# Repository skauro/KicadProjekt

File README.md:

# Raspberry Pi GPIO Hat – For raspberry pi 4B based prototype that measures video delay

This repository contains the complete KiCad project files, Gerber output, and a .rar archive package intended for PCB manufacturing and modification. The design is a custom Raspberry Pi HAT (Hardware Attached on Top) tailored for GPIO interfacing with USB and RJ45 port alignment for an enclosure.

## 📷 Overview
 It features:
 
- **Raspberry Pi 40-pin GPIO header** for direct stacking.
- **Two push-button switches**:
  - `SW1`: Momentary tactile push button
  - `SW2`: SPDT switch footprint
- **Supporting components**:
  - Capacitors (10µF, 100nF) for decoupling
  - Resistors (e.g., 10Ω) for current limiting or signal conditioning
  - LED (D2) indicator
- A mostly top-layer signal layout with a ground pour to ensure good electrical performance.

## 📁 Contents
├── gerber/ # Gerber files for manufacturing

├── *.kicad_sch # Schematic

├── *.kicad_pcb # PCB layout

├── Gerbers.rar # Pre-packaged archive to send to PCB manufacturer

└── README.md # This file

🛠️ How to Use
For Fabrication:
Send the contents of the Gerbers.rar or the /gerber/ folder to your preferred PCB manufacturer. Most PCB suppliers accept this standard format.

For Modification:
Clone or download this repository.

Open the .kicad_pro file using KiCad (version 7+ recommended).

Modify the schematic or PCB layout as needed.

Re-export the Gerber files from KiCad.

📦 Recommended PCB Specs
2-layer board

1.6mm FR-4

📄 License
This project is open for any use. If you plan to commercialize it, please contact the original author or fork appropriately.

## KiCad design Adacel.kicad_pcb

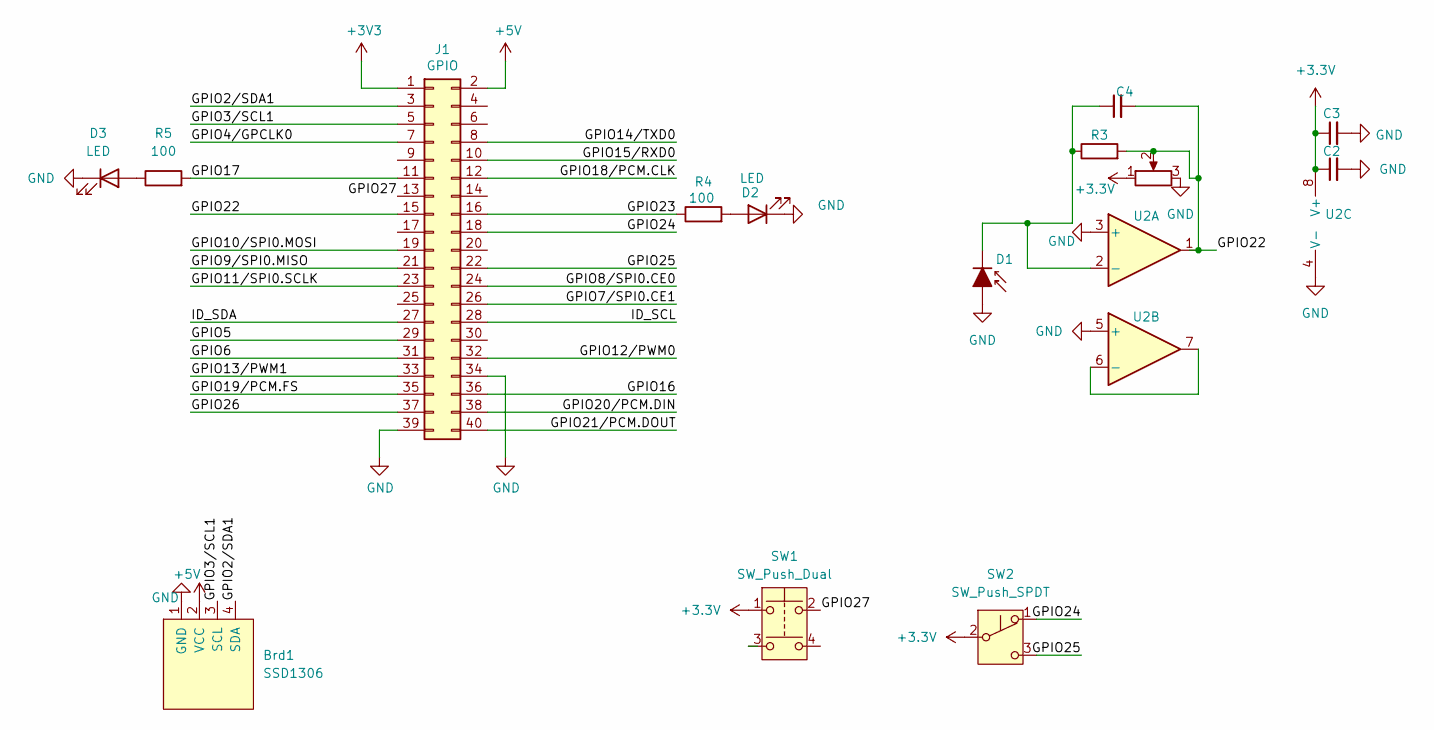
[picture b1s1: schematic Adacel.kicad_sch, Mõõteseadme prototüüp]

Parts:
Brd1: SSD1306; PinSocket_1x04_P2.00mm_Vertical
C2: 10uF; C_Rect_L10.3mm_W7.2mm_P7.50mm_MKS4
C3: 100nF; CP_Radial_D5.0mm_P2.50mm
C4: 22pF; C_Disc_D5.0mm_W2.5mm_P2.50mm
D1: LED_D5.0mm_IRGrey
D2, D3: LED; LED_D5.0mm
J1: GPIO; PinSocket_2x20_P2.54mm_Vertical
R3: 900k; R_Axial_DIN0414_L11.9mm_D4.5mm_P5.08mm_Vertical
R4, R5: 100; R_Axial_DIN0414_L11.9mm_D4.5mm_P5.08mm_Vertical
RV1: 220k; Potentiometer_Piher_PT-10-H01_Horizontal
SW1: SW_Push_Dual; SW_PUSH_6mm
SW2: SW_Push_SPDT; SW_Slide-03_Wuerth-WS-SLTV_10x2.5x6.4_P2.54mm
U2: DIP-8_W7.62mm_Socket_LongPads

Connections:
+5V: Brd1.2 (VCC), J1.2
/GPIO2/SDA1: Brd1.4 (SDA), J1.3
/GPIO3/SCL1: Brd1.3 (SCL), J1.5
/GPIO4/GPCLK0: J1.7
/GPIO5: J1.29
/GPIO6: J1.31
/GPIO7/SPI0.CE1: J1.26
/GPIO8/SPI0.CE0: J1.24
/GPIO9/SPI0.MISO: J1.21
/GPIO10/SPI0.MOSI: J1.19
/GPIO11/SPI0.SCLK: J1.23
/GPIO12/PWM0: J1.32
/GPIO13/PWM1: J1.33
/GPIO14/TXD0: J1.8
/GPIO15/RXD0: J1.10
/GPIO16: J1.36
/GPIO17: J1.11, R5.2
/GPIO18/PCM.CLK: J1.12
/GPIO19/PCM.FS: J1.35
/GPIO20/PCM.DIN: J1.38
/GPIO21/PCM.DOUT: J1.40
/GPIO22: C4.2, J1.15, R3.2, RV1.2, U2.1
/GPIO23: J1.16, R4.1
/GPIO24: J1.18, SW2.1 (A)
/GPIO25: J1.22, SW2.3 (C)
/GPIO26: J1.37
/GPIO27: J1.13, SW1.2
/ID_SCL: J1.28
/ID_SDA: J1.27
GND: Brd1.1 (GND), C2.2, C3.2, D1.2 (A), D2.1 (K), D3.1 (K), J1.34, J1.39, RV1.3, U2.3 (+), U2.4 (V-), U2.5 (+)
unnamed: C4.1, D1.1 (K), R3.1, U2.2 (-)
unnamed: D2.2 (A), R4.2
unnamed: D3.2 (A), R5.1
unnamed: U2.6 (-), U2.7

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
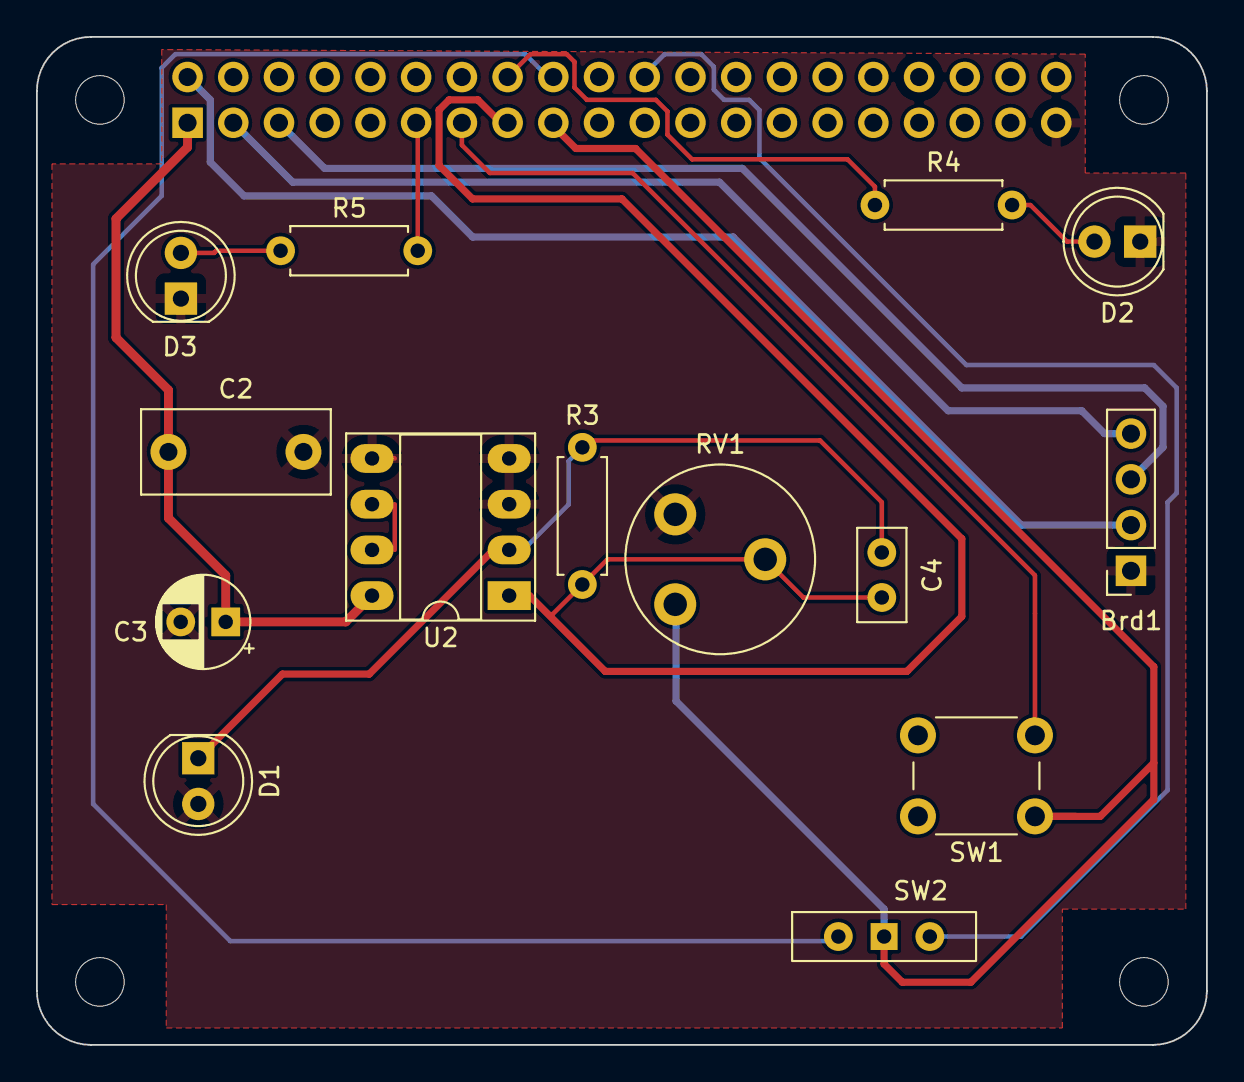
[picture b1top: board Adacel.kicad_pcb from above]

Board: 2 copper layers, 65.0 x 56.0 mm, 19 parts (1 on the bottom side), 15 nets.

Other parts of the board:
MH1, MH2, MH3, MH4: MountingHole_2.7mm_M2.5

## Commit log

2025-03-21 added kicad files
2025-05-07 final gerber files
2025-05-07 new gerber zip
